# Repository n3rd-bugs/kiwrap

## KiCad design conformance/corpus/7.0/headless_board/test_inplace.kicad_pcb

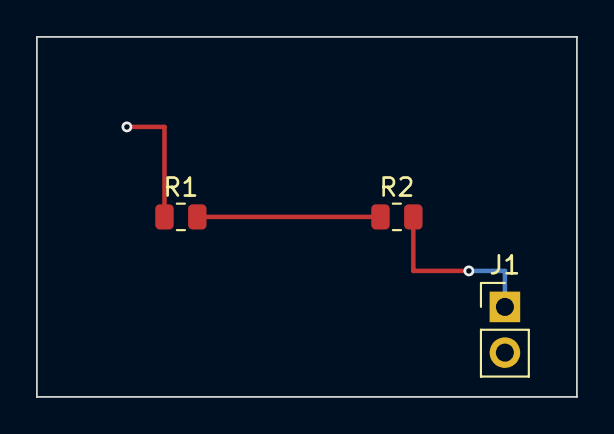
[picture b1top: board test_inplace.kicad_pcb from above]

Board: 2 copper layers, 30.0 x 20.0 mm, 3 parts (0 on the bottom side), 3 nets.

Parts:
J1: PinHeader_1x02_P2.54mm_Vertical
R1, R2: R_0805_2012Metric

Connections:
GND: J1.2, R1.1
SIG: R1.2, R2.1
VCC: J1.1, R2.2
